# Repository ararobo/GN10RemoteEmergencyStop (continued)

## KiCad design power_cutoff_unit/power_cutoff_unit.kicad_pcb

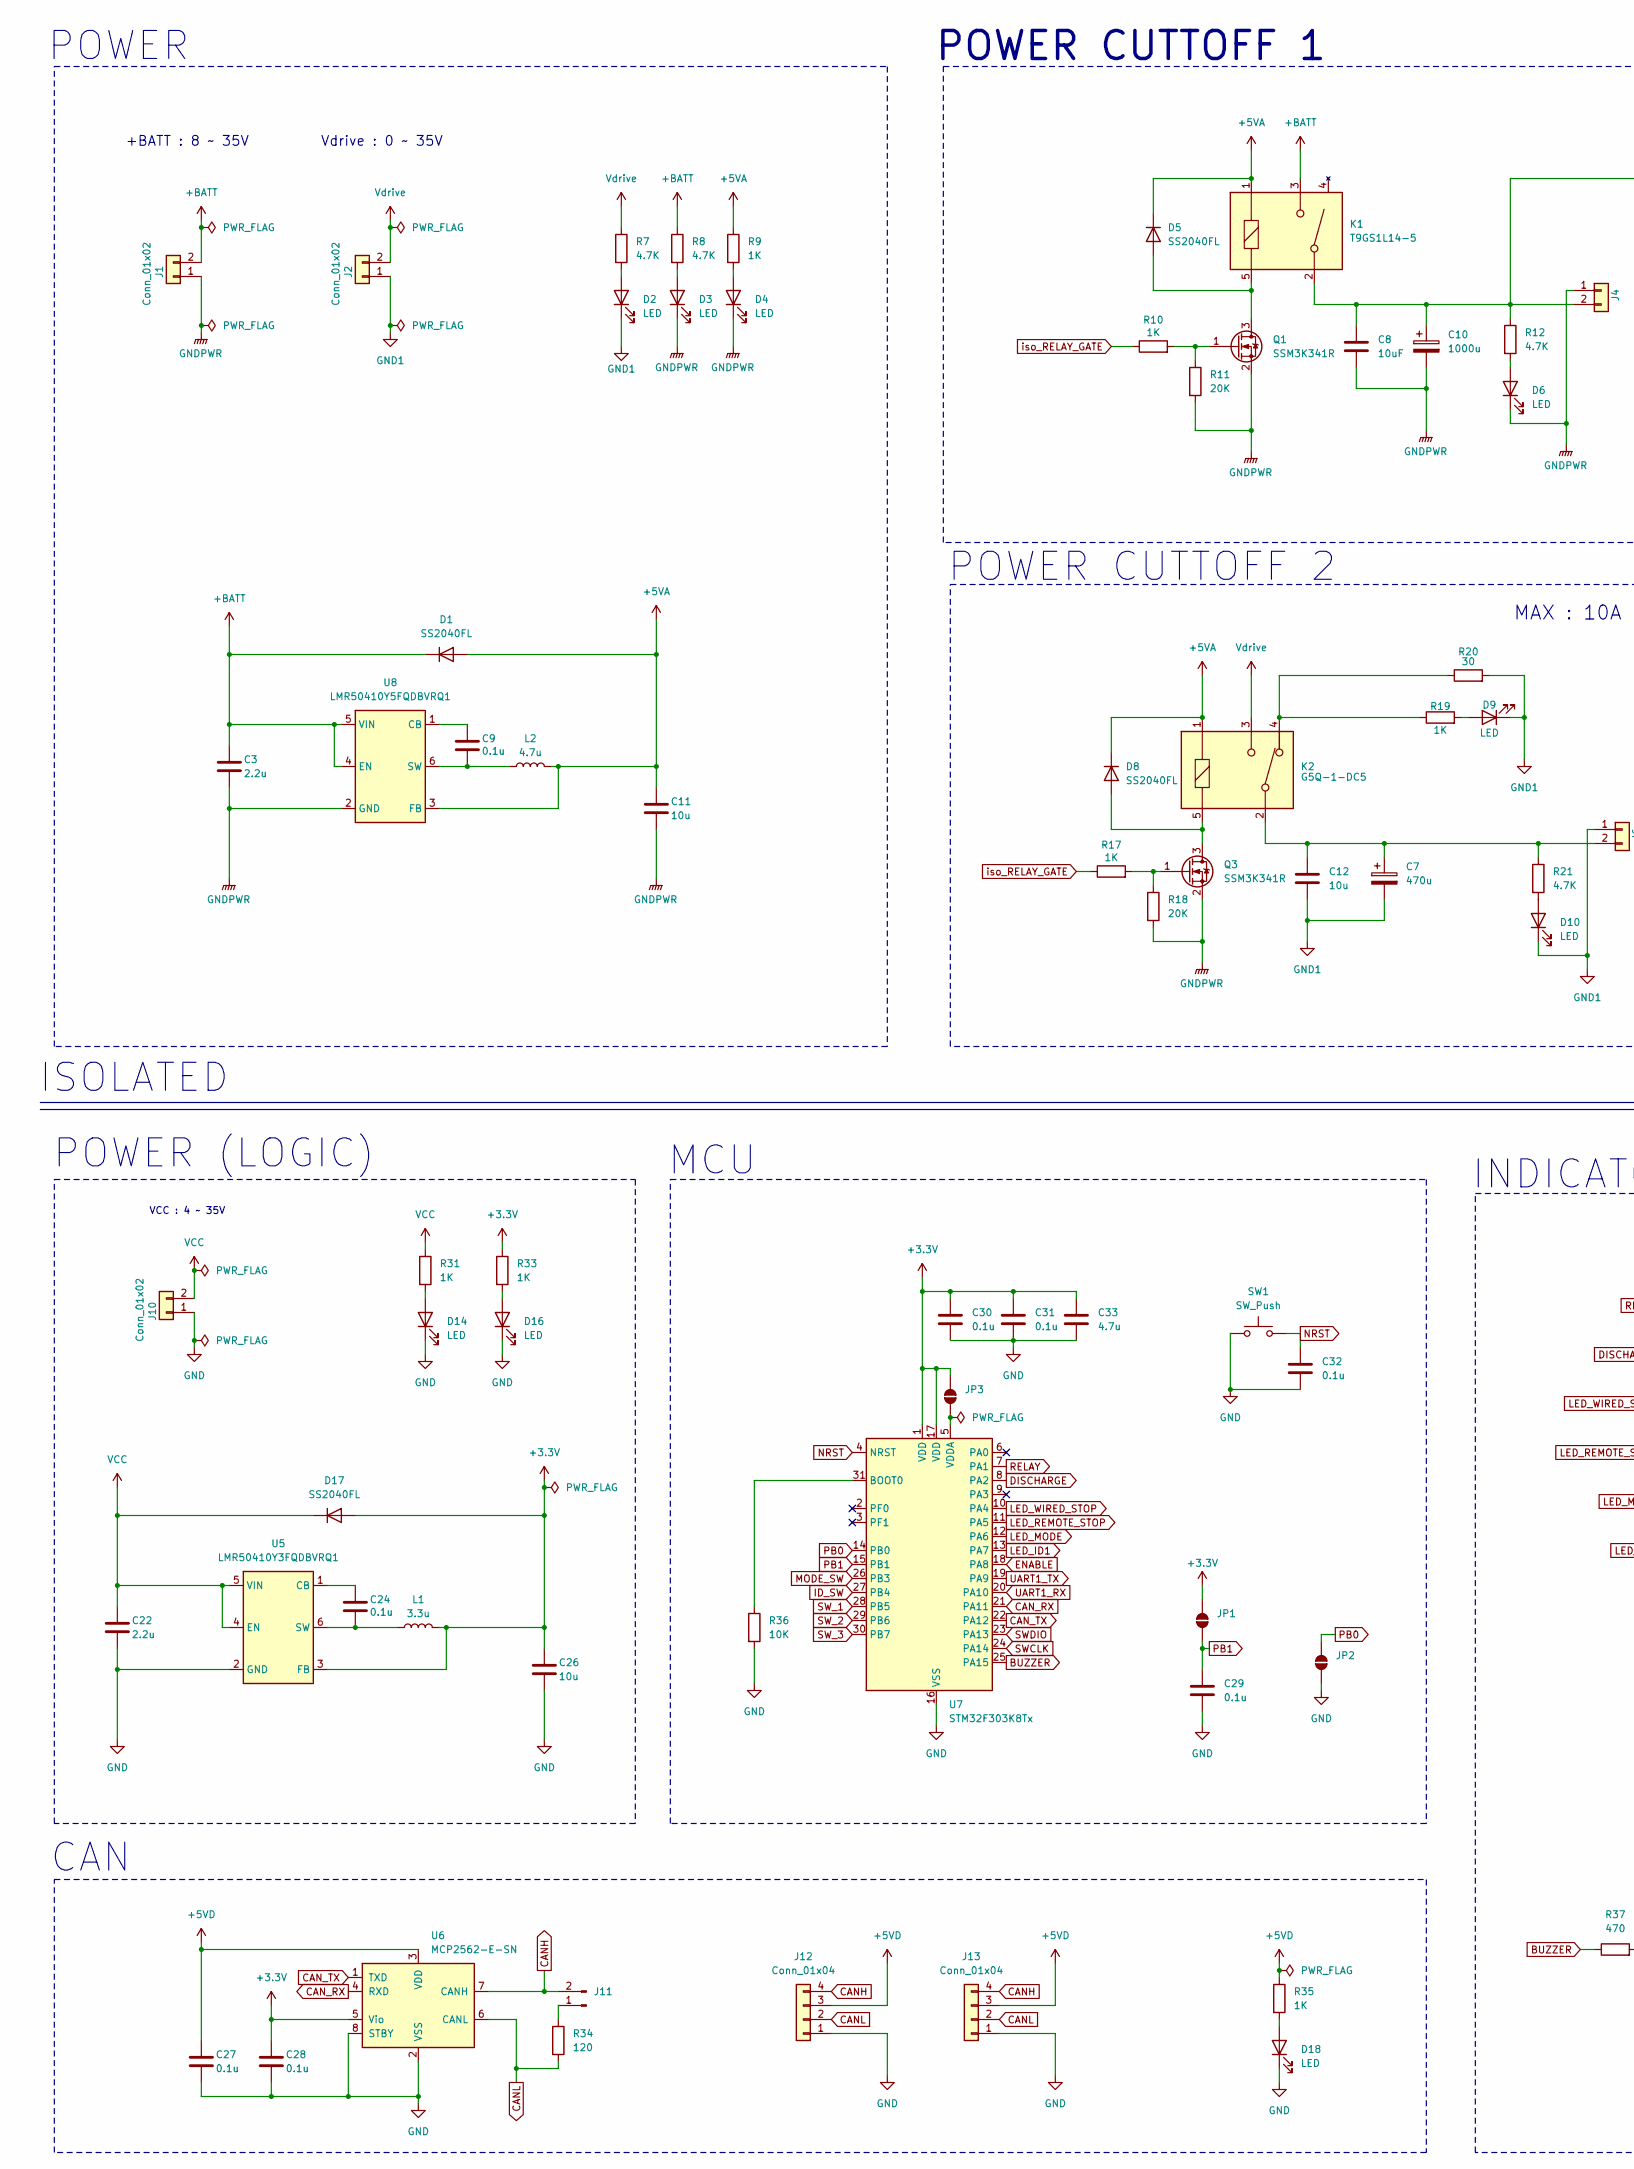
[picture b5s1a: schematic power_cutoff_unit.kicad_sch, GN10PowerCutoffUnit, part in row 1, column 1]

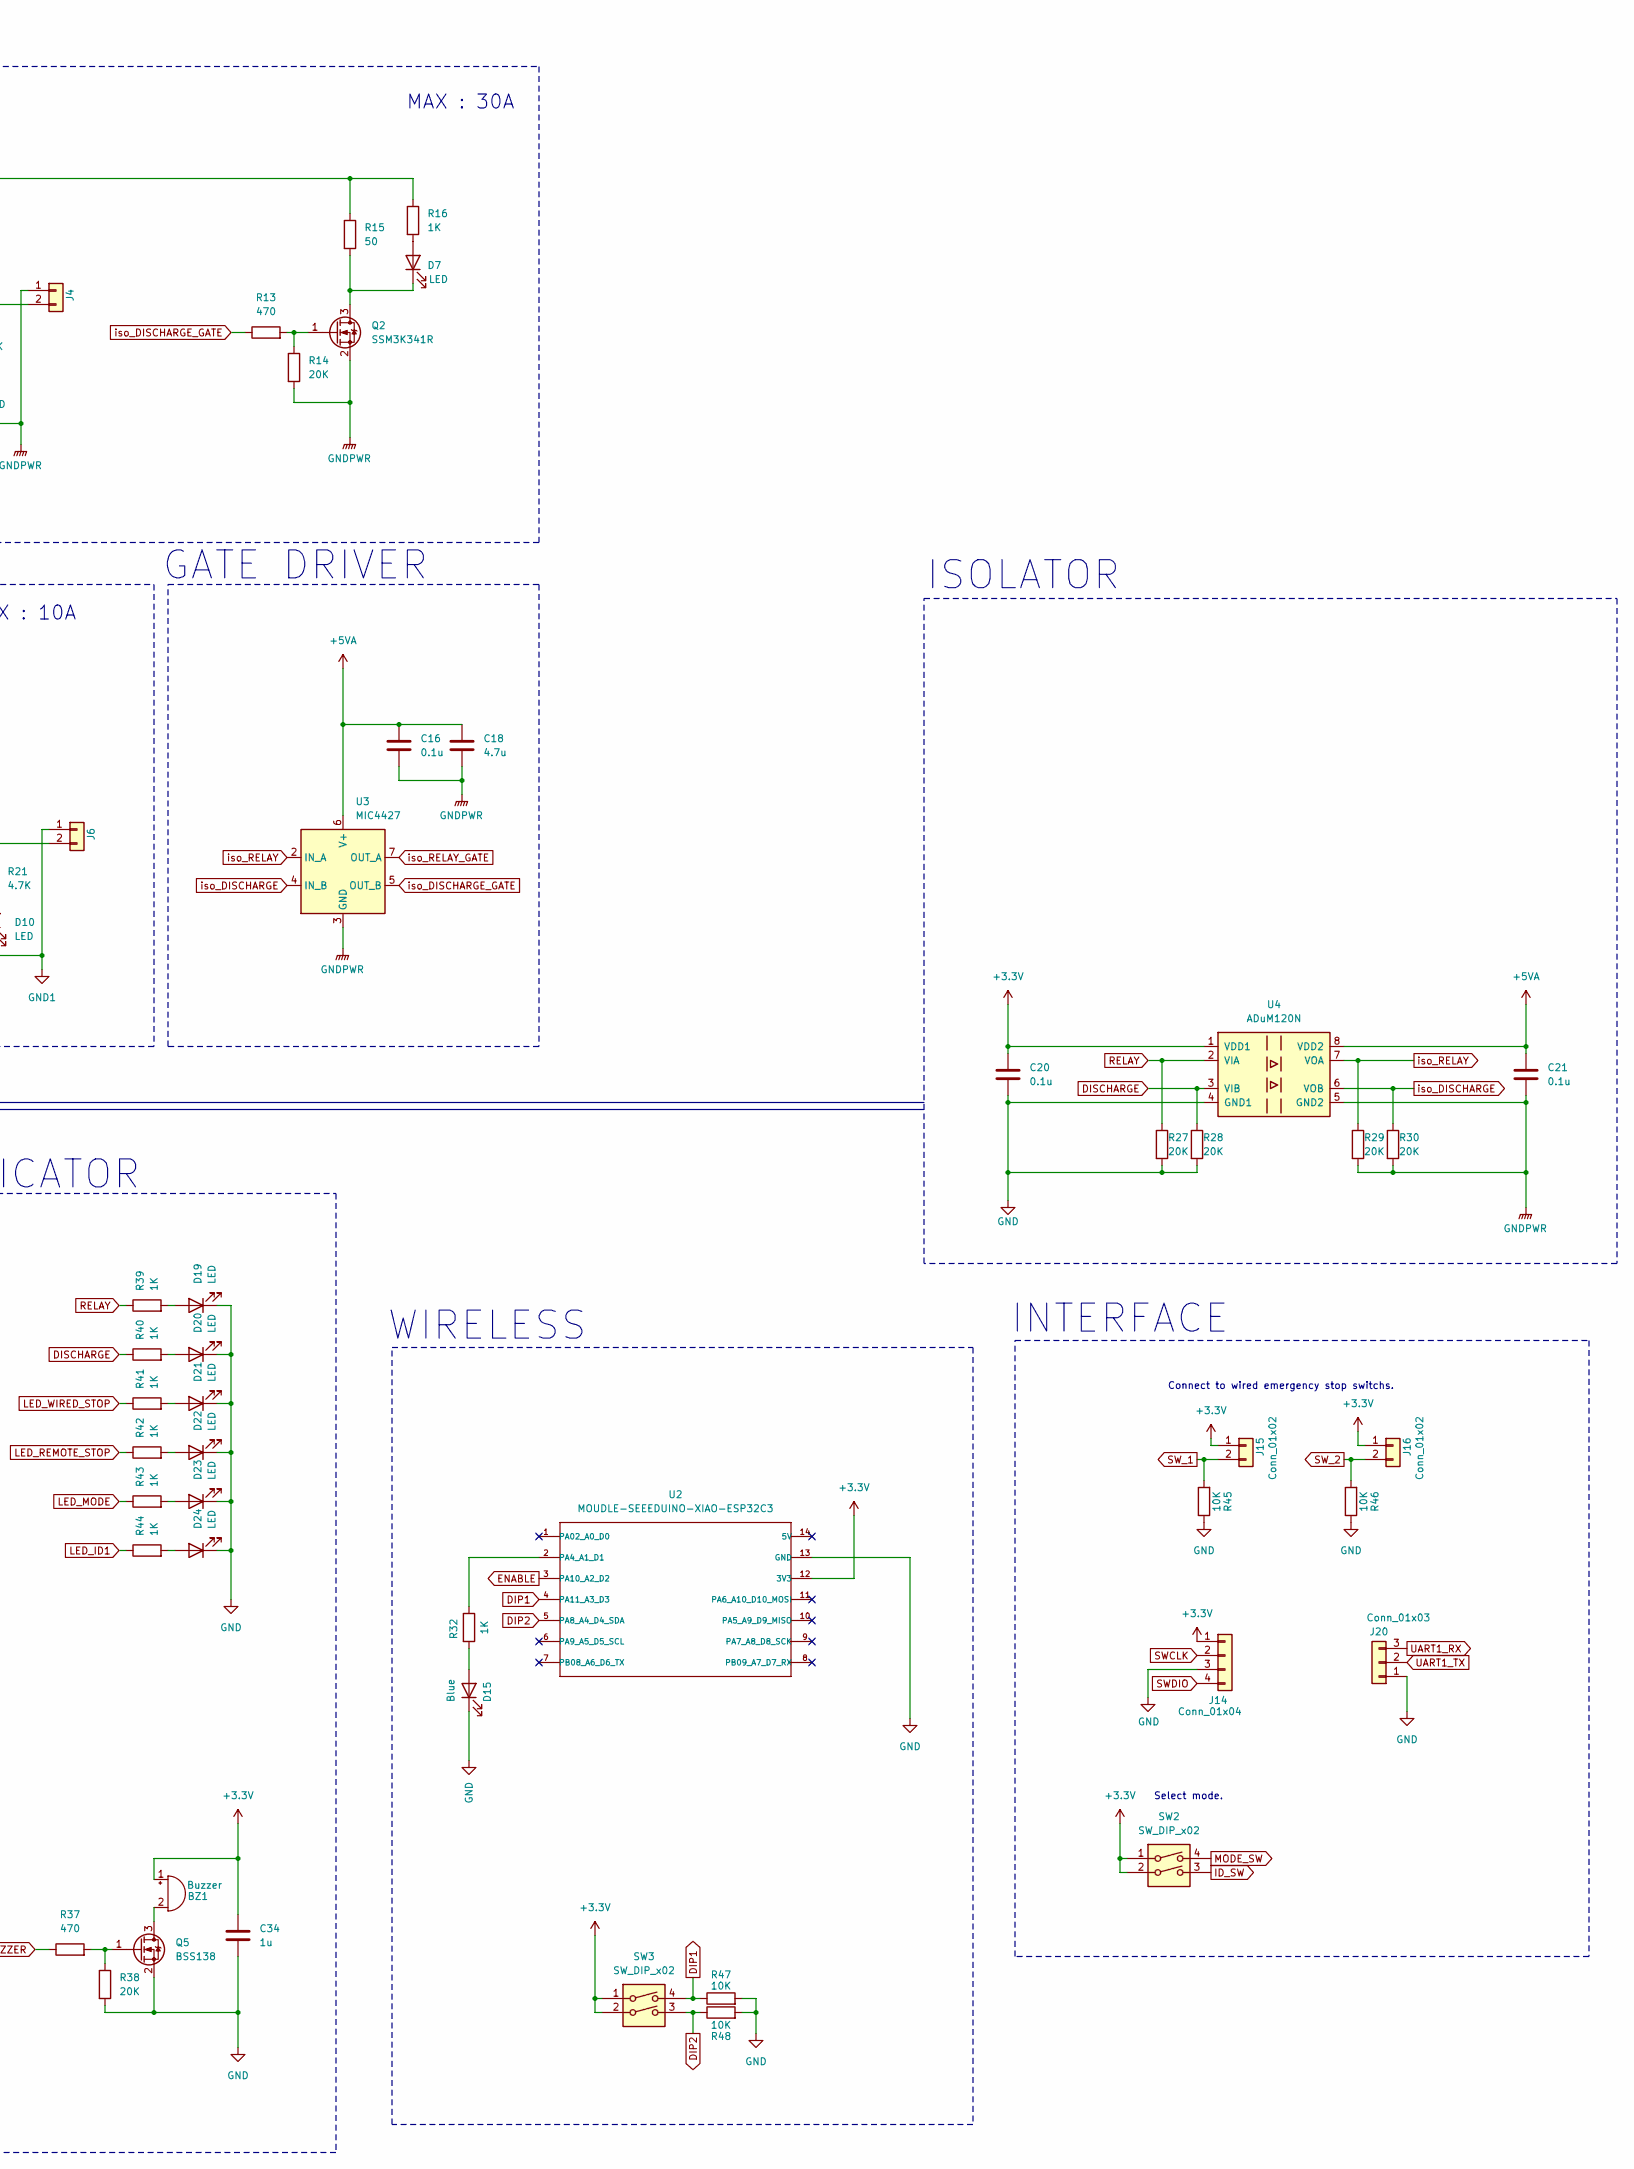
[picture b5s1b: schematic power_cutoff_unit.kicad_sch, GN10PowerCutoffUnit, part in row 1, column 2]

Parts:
BZ1: Buzzer; Buzzer_12x9.5RM7.6
C3, C22: 2.2u; C_0805_2012Metric
C7: 470u; CP_Radial_D12.5mm_P5.00mm
C8: 10uF; C_0805_2012Metric
C9, C16, C20, C21, C24, C27, C28, C29, C30, C31, C32: 0.1u; C_0402_1005Metric
C10: 1000u; CP_Radial_D16.0mm_P7.50mm
C11, C12, C26: 10u; C_0805_2012Metric
C18, C33: 4.7u; C_0603_1608Metric
C34: 1u; C_0402_1005Metric
D1, D5, D8, D17: SS2040FL; D_SOD-123F
D2, D3, D4, D6, D7, D9, D10, D14, D16, D18, D19, D20, D21, D22, D23, D24: LED; LED_0603_1608Metric
D15: Blue; LED_0603_1608Metric_Pad1.05x0.95mm_HandSolder
J1, J2: Conn_01x02; AMASS_XT60PW-M_1x02_P7.20mm_Horizontal
J4, J6: Conn_01x02; AMASS_XT60PW-F_1x02_P7.20mm_Horizontal
J10: Conn_01x02; AMASS_XT30U-M_1x02_P5.0mm_Vertical
J11: Conn_01x02_Pin; PinHeader_1x02_P2.54mm_Vertical
J12, J13: Conn_01x04; JST_XH_B4B-XH-A_1x04_P2.50mm_Vertical
J14: Conn_01x04; PinHeader_1x04_P2.54mm_Vertical
J15, J16: Conn_01x02; JST_XH_B2B-XH-A_1x02_P2.50mm_Vertical
J20: Conn_01x03; PinHeader_1x03_P2.54mm_Vertical
JP1, JP2, JP3: SolderJumper_2_Open; SolderJumper-2_P1.3mm_Open_RoundedPad1.0x1.5mm
K1: T9GS1L14-5; T9G
K2: G5Q-1-DC5; G5Q-1
L1: 3.3u; DEM2818C
L2: 4.7u; DEM2818C
Q1, Q2, Q3: SSM3K341R; SOT-23_Handsoldering
Q5: BSS138; SOT-23
R7, R8, R12, R21: 4.7K; R_0603_1608Metric
R9, R16, R19, R32: 1K; R_0402_1005Metric
R10, R17, R31, R33, R35, R39, R40, R41, R42, R43, R44: 1K; R_0603_1608Metric
R11, R14, R18, R27, R28, R29, R30, R38: 20K; R_0603_1608Metric
R13, R37: 470; R_0603_1608Metric
R15: 50; TO-263-2_TabPin1
R20: 30; TO-263-2_TabPin1
R34: 120; R_0603_1608Metric
R36, R45, R46, R47, R48: 10K; R_0603_1608Metric
SW1: SW_Push; SKRPABE010
SW2, SW3: SW_DIP_x02; SW_DIP_SPSTx02_Slide_Omron_A6H-2101_W6.15mm_P1.27mm
U2: MOUDLE-SEEEDUINO-XIAO-ESP32C3; MCU_Seeed_ESP32C3
U3: MIC4427; SOIC-8_3.9x4.9mm_P1.27mm
U4: ADuM120N; SOIC-8_3.9x4.9mm_P1.27mm
U5: LMR50410Y3FQDBVRQ1; SOT-23-6
U6: MCP2562-E-SN; SOIC-8_3.9x4.9mm_P1.27mm
U7: STM32F303K8Tx; LQFP-32_7x7mm_P0.8mm
U8: LMR50410Y5FQDBVRQ1; SOT-23-6

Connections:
+3.3V: BZ1.1 (+), C20.1, C26.1, C28.1, C30.1, C31.1, C33.1, C34.1, D17.2 (A), J14.1, J15.1, J16.1, JP1.2 (B), JP3.2 (B), L1.2, R33.1, SW2.1, SW2.2, SW3.1, SW3.2, U2.12 (3V3), U4.1 (VDD1), U5.3 (FB), U6.5 (Vio), U7.1 (VDD), U7.17 (VDD)
+5VA: C11.1, C16.1, C18.1, C21.1, D1.2 (A), D5.1 (K), D8.1 (K), K1.1, K2.1, L2.2, R9.1, U3.6 (V+), U4.8 (VDD2), U8.3 (FB)
+5VD: C27.1, J12.3, J13.3, R35.1, U6.3 (VDD)
+BATT: C3.1, D1.1 (K), J1.2, K1.3, R8.1, U8.4 (EN), U8.5 (VIN)
BUZZER: R37.1, U7.25 (PA15)
CANH: J11.2, J12.4, J13.4, U6.7 (CANH)
CANL: J12.2, J13.2, R34.2, U6.6 (CANL)
CAN_RX: U6.4 (RXD), U7.21 (PA11)
CAN_TX: U6.1 (TXD), U7.22 (PA12)
DIP1: R47.1, SW3.4, U2.4 (PA11_A3_D3)
DIP2: R48.1, SW3.3, U2.5 (PA8_A4_D4_SDA)
DISCHARGE: R28.1, R40.1, U4.3 (VIB), U7.8 (PA2)
ENABLE: U2.3 (PA10_A2_D2), U7.18 (PA8)
GND: C20.2, C22.2, C26.2, C27.2, C28.2, C29.2, C30.2, C31.2, C32.2, C33.2, C34.2, D14.1 (K), D15.1 (K), D16.1 (K), D18.1 (K), D19.1 (K), D20.1 (K), D21.1 (K), D22.1 (K), D23.1 (K), D24.1 (K), J10.1, J12.1, J13.1, J14.3, J20.1, JP2.1 (A), Q5.2 (S), R27.2, R28.2, R36.2, R38.2, R45.1, R46.1, R47.2, R48.2, SW1.1, U2.13 (GND), U4.4 (GND1), U5.2 (GND), U6.2 (VSS), U6.8 (STBY), U7.16 (VSS), U7.32 (VSS)
GND1: C7.2, C12.2, D2.1 (K), D9.1 (K), D10.1 (K), J2.1, J6.1, R20.2
GNDPWR: C3.2, C8.2, C10.2, C11.2, C16.2, C18.2, C21.2, D3.1 (K), D4.1 (K), D6.1 (K), J1.1, J4.1, Q1.2 (S), Q2.2 (S), Q3.2 (S), R11.2, R14.2, R18.2, R29.2, R30.2, U3.3 (GND), U4.5 (GND2), U8.2 (GND)
ID_SW: SW2.3, U7.27 (PB4)
LED_ID1: R44.1, U7.13 (PA7)
LED_MODE: R43.1, U7.12 (PA6)
LED_REMOTE_STOP: R42.1, U7.11 (PA5)
LED_WIRED_STOP: R41.1, U7.10 (PA4)
MODE_SW: SW2.4, U7.26 (PB3)
NRST: C32.1, SW1.2, U7.4 (NRST)
unnamed: BZ1.2 (-), Q5.3 (D)
unnamed: D2.2 (A), R7.2
unnamed: D3.2 (A), R8.2
unnamed: D4.2 (A), R9.2
unnamed: D5.2 (A), K1.5, Q1.3 (D)
unnamed: D6.2 (A), R12.2
unnamed: D7.2 (A), R16.2
unnamed: D7.1 (K), Q2.3 (D), R15.2
unnamed: D8.2 (A), K2.5, Q3.3 (D)
unnamed: D9.2 (A), R19.2
unnamed: D10.2 (A), R21.2
unnamed: D14.2 (A), R31.2
unnamed: D15.2 (A), R32.2
unnamed: D16.2 (A), R33.2
unnamed: D18.2 (A), R35.2
unnamed: D19.2 (A), R39.2
unnamed: D20.2 (A), R40.2
unnamed: D21.2 (A), R41.2
unnamed: D22.2 (A), R42.2
unnamed: D23.2 (A), R43.2
unnamed: D24.2 (A), R44.2
unnamed: C8.1, C10.1, J4.2, K1.2, R12.1, R15.1, R16.1
unnamed: C7.1, C12.1, J6.2, K2.2, R21.1
unnamed: J11.1, R34.1
unnamed: JP3.1 (A), U7.5 (VDDA)
unnamed: K2.4, R19.1, R20.1
unnamed: Q1.1 (G), R10.2, R11.1
unnamed: Q2.1 (G), R13.2, R14.1
unnamed: Q3.1 (G), R17.2, R18.1
unnamed: Q5.1 (G), R37.2, R38.1
unnamed: R32.1, U2.2 (PA4_A1_D1)
unnamed: C24.1, U5.1 (CB)
unnamed: C24.2, L1.1, U5.6 (SW)
unnamed: R36.1, U7.31 (BOOT0)
unnamed: C9.1, U8.1 (CB)
unnamed: C9.2, L2.1, U8.6 (SW)
PB0: JP2.2 (B), U7.14 (PB0)
PB1: C29.1, JP1.1 (A), U7.15 (PB1)
RELAY: R27.1, R39.1, U4.2 (VIA), U7.7 (PA1)
SWCLK: J14.2, U7.24 (PA14)
SWDIO: J14.4, U7.23 (PA13)
SW_1: J15.2, R45.2, U7.28 (PB5)
SW_2: J16.2, R46.2, U7.29 (PB6)
SW_3: U7.30 (PB7)
UART1_RX: J20.3, U7.20 (PA10)
UART1_TX: J20.2, U7.19 (PA9)
VCC: C22.1, D17.1 (K), J10.2, R31.1, U5.4 (EN), U5.5 (VIN)
Vdrive: J2.2, K2.3, R7.1
iso_DISCHARGE: R30.1, U3.4 (IN_B), U4.6 (VOB)
iso_DISCHARGE_GATE: R13.1, U3.5 (OUT_B)
iso_RELAY: R29.1, U3.2 (IN_A), U4.7 (VOA)
iso_RELAY_GATE: R10.1, R17.1, U3.7 (OUT_A)

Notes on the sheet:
ISOLATED
INDICATOR
POWER CUTTOFF 1
WIRELESS
POWER
MCU
POWER CUTTOFF 2
INTERFACE
VCC : 4 ~ 35V
+BATT : 8 ~ 35V
Connect to wired emergency stop switchs.
POWER (LOGIC)
CAN
ISOLATOR
Vdrive : 0 ~ 35V
GATE DRIVER
MAX : 10A
MAX : 30A
Select mode.

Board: 2 copper layers, 113 parts (21 on the bottom side), 74 nets, no tracks yet.

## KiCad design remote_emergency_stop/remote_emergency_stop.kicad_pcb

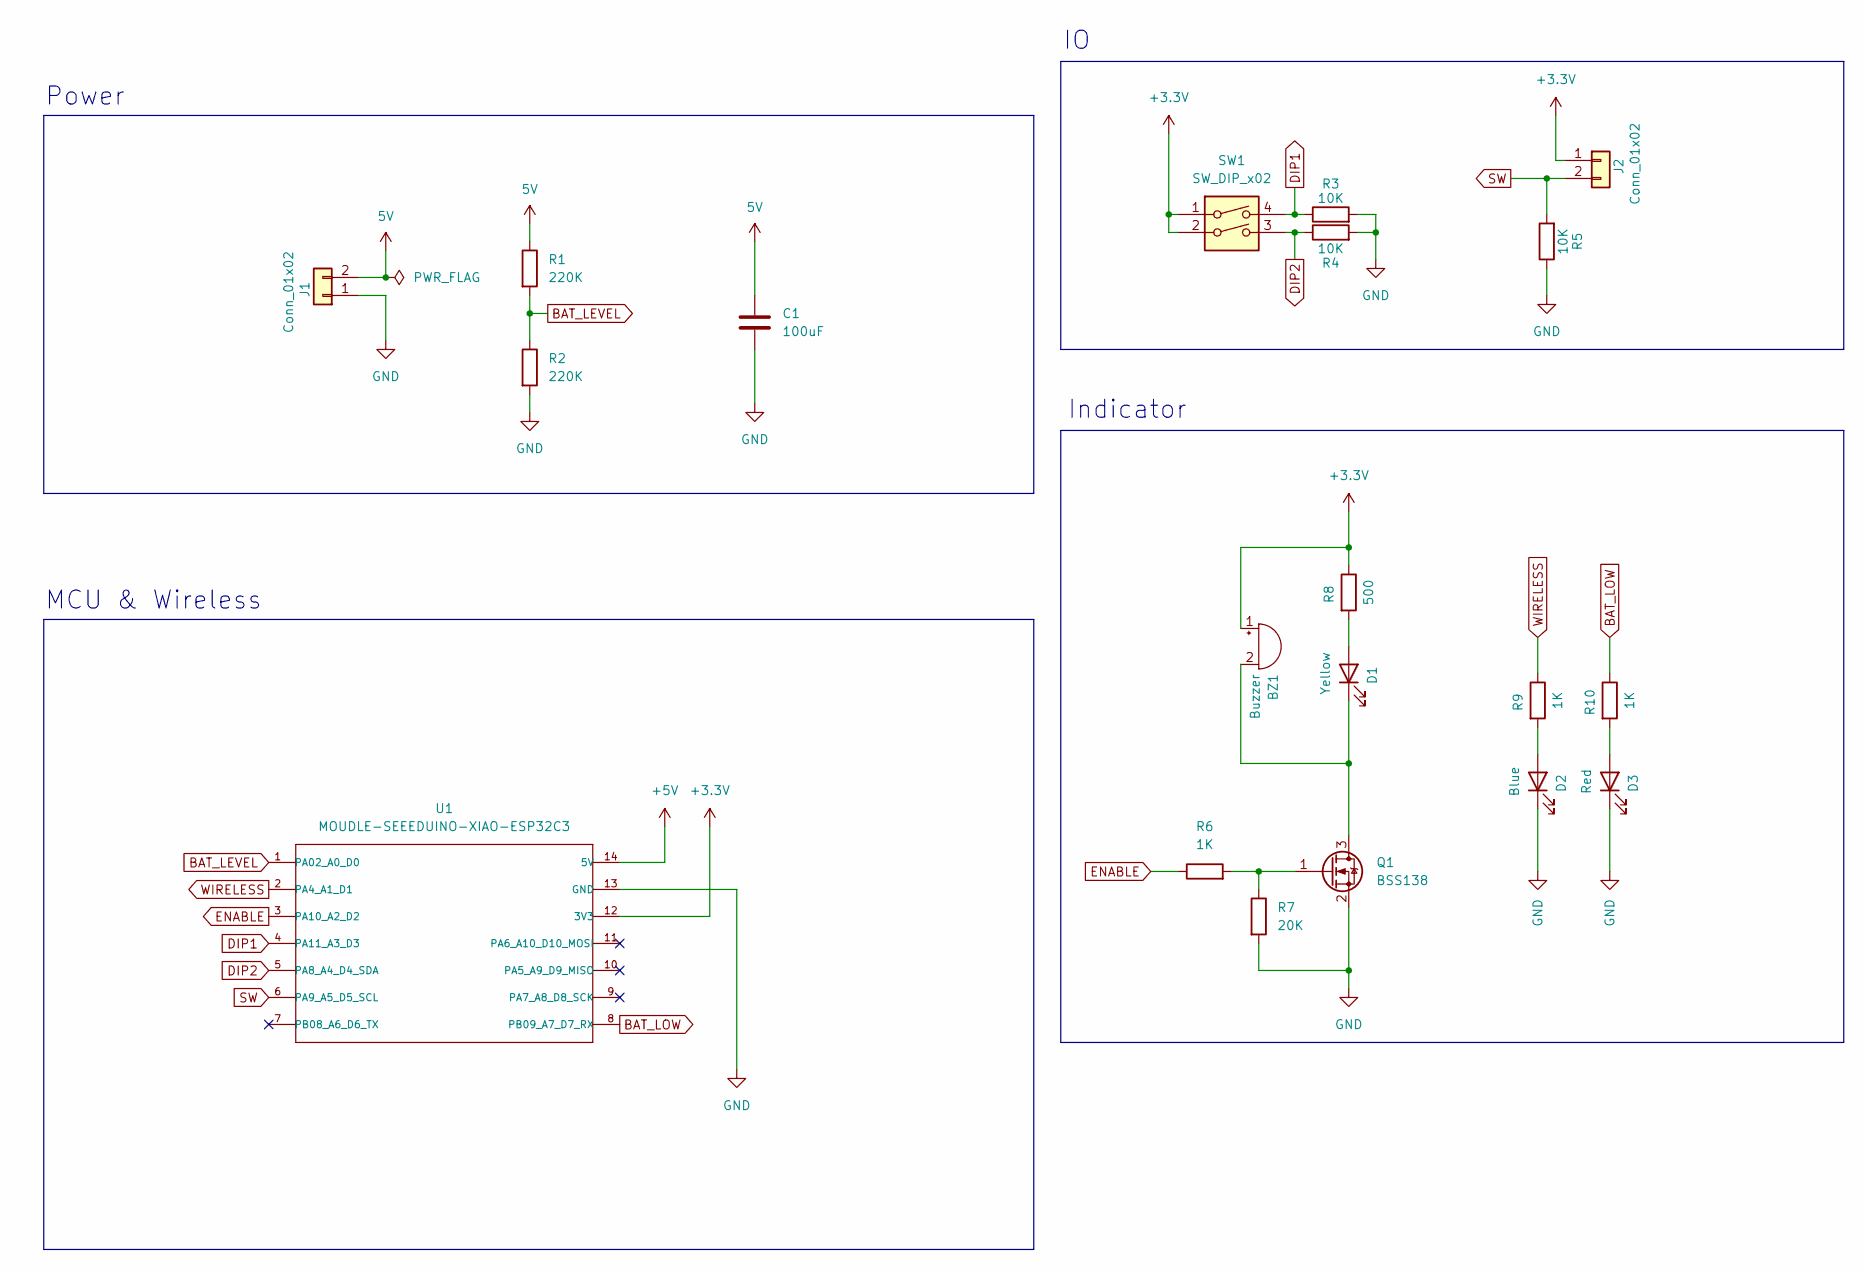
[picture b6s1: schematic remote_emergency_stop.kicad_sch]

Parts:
BZ1: Buzzer; Buzzer_12x9.5RM7.6
C1: 100uF; CP_Radial_D5.0mm_P2.00mm
D1: Yellow; LED_0603_1608Metric_Pad1.05x0.95mm_HandSolder
D2: Blue; LED_0603_1608Metric_Pad1.05x0.95mm_HandSolder
D3: Red; LED_0603_1608Metric_Pad1.05x0.95mm_HandSolder
J1: Conn_01x02; AMASS_XT30PW-M_1x02_P2.50mm_Horizontal
J2: Conn_01x02; JST_XH_S2B-XH-A_1x02_P2.50mm_Horizontal
Q1: BSS138; SOT-23
R1, R2: 220K; R_0603_1608Metric
R3, R4, R5: 10K; R_0603_1608Metric
R6, R9, R10: 1K; R_0603_1608Metric
R7: 20K; R_0603_1608Metric
R8: 500; R_0603_1608Metric
SW1: SW_DIP_x02; SW_DIP_SPSTx02_Slide_Omron_A6H-2101_W6.15mm_P1.27mm
U1: MOUDLE-SEEEDUINO-XIAO-ESP32C3; MCU_Seeed_ESP32C3

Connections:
5V: C1.1, J1.2, R1.1
+3.3V: BZ1.1 (+), J2.1, R8.1, SW1.1, SW1.2, U1.12 (3V3)
+5V: U1.14 (5V)
BAT_LEVEL: R1.2, R2.1, U1.1 (PA02_A0_D0)
BAT_LOW: R10.1, U1.8 (PB09_A7_D7_RX)
DIP1: R3.1, SW1.4, U1.4 (PA11_A3_D3)
DIP2: R4.1, SW1.3, U1.5 (PA8_A4_D4_SDA)
ENABLE: R6.1, U1.3 (PA10_A2_D2)
GND: C1.2, D2.1 (K), D3.1 (K), J1.1, Q1.2 (S), R2.2, R3.2, R4.2, R5.1, R7.2, U1.13 (GND)
unnamed: BZ1.2 (-), D1.1 (K), Q1.3 (D)
unnamed: D1.2 (A), R8.2
unnamed: D2.2 (A), R9.2
unnamed: D3.2 (A), R10.2
unnamed: Q1.1 (G), R6.2, R7.1
SW: J2.2, R5.2, U1.6 (PA9_A5_D5_SCL)
WIRELESS: R9.1, U1.2 (PA4_A1_D1)

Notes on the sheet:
MCU & Wireless
Indicator
Power

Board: 2 copper layers, 20 parts (0 on the bottom side), 15 nets, no tracks yet.

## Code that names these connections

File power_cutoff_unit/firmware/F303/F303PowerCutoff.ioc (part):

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Mcu.Name=STM32F303K(6-8)Tx
Mcu.Package=LQFP32
Mcu.UserName=STM32F303K8Tx
PA1.GPIOParameters=GPIO_Label
PA1.GPIO_Label=DISCHARGE
PA1.Signal=GPIO_Output
PA10.Mode=Asynchronous
PA10.Signal=USART1_RX
PA11.Mode=CAN_Activate
PA11.Signal=CAN_RX
PA12.Mode=CAN_Activate
PA12.Signal=CAN_TX
PA13.Mode=Serial_Wire
PA13.Signal=SYS_JTMS-SWDIO
PA14.Mode=Serial_Wire
PA14.Signal=SYS_JTCK-SWCLK
PA15.GPIOParameters=GPIO_Label
PA15.GPIO_Label=BUZZER
PA15.Signal=GPIO_Output
PA2.GPIOParameters=GPIO_Label
PA2.GPIO_Label=RELAY_EN
PA2.Signal=GPIO_Output
PA4.GPIOParameters=GPIO_Label
PA4.GPIO_Label=LED_WIRED_STOP
PA4.Signal=GPIO_Output
PA5.GPIOParameters=GPIO_Label
PA5.GPIO_Label=LED_REMOTE_STOP
PA5.Signal=GPIO_Output
PA6.GPIOParameters=GPIO_Label
PA6.GPIO_Label=LED_MODE
PA6.Signal=GPIO_Output
PA7.GPIOParameters=GPIO_Label
PA7.GPIO_Label=LED_ID1
PA7.Signal=GPIO_Output
PA8.GPIOParameters=GPIO_Label
PA8.GPIO_Label=ENABLE
PA8.Signal=GPIO_Input
PA9.Mode=Asynchronous
PA9.Signal=USART1_TX
PB3.GPIOParameters=GPIO_Label
PB3.GPIO_Label=DIP_1
PB3.Signal=GPIO_Input
PB4.GPIOParameters=GPIO_Label
PB4.GPIO_Label=DIP_2
PB4.Signal=GPIO_Input
PB5.GPIOParameters=GPIO_Label
PB5.GPIO_Label=SW_1
PB5.Signal=GPIO_Input
PB6.GPIOParameters=GPIO_Label
PB6.GPIO_Label=SW_2
PB6.Signal=GPIO_Input
PB7.GPIOParameters=GPIO_Label
PB7.GPIO_Label=SW_3
PB7.Signal=GPIO_Input
RCC.HSEPLLFreq_Value=8000000
RCC.HSE_VALUE=8000000
RCC.SYSCLKFreq_VALUE=64000000
RCC.SYSCLKSourceVirtual=RCC_SYSCLKSOURCE_PLLCLK
board=custom

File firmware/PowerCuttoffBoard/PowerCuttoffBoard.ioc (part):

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Mcu.Name=STM32F303K(6-8)Tx
Mcu.Package=LQFP32
Mcu.UserName=STM32F303K8Tx
PA10.Mode=Asynchronous
PA10.Signal=USART1_RX
PA11.Mode=CAN_Activate
PA11.Signal=CAN_RX
PA12.Mode=CAN_Activate
PA12.Signal=CAN_TX
PA13.Mode=Serial_Wire
PA13.Signal=SYS_JTMS-SWDIO
PA14.Mode=Serial_Wire
PA14.Signal=SYS_JTCK-SWCLK
PA15.GPIOParameters=GPIO_PuPd,GPIO_Label
PA15.GPIO_Label=DIP4
PA15.GPIO_PuPd=GPIO_PULLDOWN
PA15.Signal=GPIO_Input
PA2.Mode=Asynchronous
PA2.Signal=USART2_TX
PA3.Mode=Asynchronous
PA3.Signal=USART2_RX
PA5.GPIOParameters=GPIO_Label
PA5.GPIO_Label=LED2
PA5.Signal=GPIO_Output
PA6.GPIOParameters=GPIO_Label
PA6.GPIO_Label=LED1
PA6.Signal=GPIO_Output
PA7.GPIOParameters=GPIO_Label
PA7.GPIO_Label=LED_CONNECTION
PA7.Signal=GPIO_Output
PA9.Mode=Asynchronous
PA9.Signal=USART1_TX
PB0.GPIOParameters=GPIO_Label
PB0.GPIO_Label=LED_DEBUG
PB0.Signal=GPIO_Output
PB1.GPIOParameters=GPIO_Label
PB1.GPIO_Label=LED_ERROR
PB1.Signal=GPIO_Output
PB3.GPIOParameters=GPIO_PuPd,GPIO_Label
PB3.GPIO_Label=DIP3
PB3.GPIO_PuPd=GPIO_PULLDOWN
PB3.Signal=GPIO_Input
PB4.GPIOParameters=GPIO_PuPd,GPIO_Label
PB4.GPIO_Label=DIP2
PB4.GPIO_PuPd=GPIO_PULLDOWN
PB4.Signal=GPIO_Input
PB5.GPIOParameters=GPIO_PuPd,GPIO_Label
PB5.GPIO_Label=DIP1
PB5.GPIO_PuPd=GPIO_PULLDOWN
PB5.Signal=GPIO_Input
PB6.GPIOParameters=GPIO_Label
PB6.GPIO_Label=RELAY_A
PB6.Signal=GPIO_Output
PB7.GPIOParameters=GPIO_Label
PB7.GPIO_Label=RELAY_B
PB7.Signal=GPIO_Output
RCC.HSEPLLFreq_Value=16000000
RCC.HSE_VALUE=16000000
RCC.SYSCLKFreq_VALUE=64000000
RCC.SYSCLKSourceVirtual=RCC_SYSCLKSOURCE_PLLCLK
board=custom

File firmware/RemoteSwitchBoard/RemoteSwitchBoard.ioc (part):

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Mcu.Name=STM32F303K(6-8)Tx
Mcu.Package=LQFP32
Mcu.UserName=STM32F303K8Tx
PA0.GPIOParameters=GPIO_Label
PA0.GPIO_Label=Buzzer
PA0.Signal=GPIO_Output
PA1.GPIOParameters=GPIO_PuPd,GPIO_Label
PA1.GPIO_Label=emstop
PA1.GPIO_PuPd=GPIO_PULLDOWN
PA1.Signal=GPIO_Input
PA10.Mode=Asynchronous
PA10.Signal=USART1_RX
PA11.GPIOParameters=GPIO_Label
PA11.GPIO_Label=LED_5
PA11.Signal=GPIO_Output
PA12.GPIOParameters=GPIO_Label
PA12.GPIO_Label=LED_6
PA12.Signal=GPIO_Output
PA13.Signal=SYS_JTMS-SWDIO
PA14.Signal=SYS_JTCK-SWCLK
PA15.GPIOParameters=GPIO_PuPd,GPIO_Label
PA15.GPIO_Label=DIP_4
PA15.GPIO_PuPd=GPIO_PULLDOWN
PA15.Signal=GPIO_Input
PA2.Mode=Asynchronous
PA2.Signal=USART2_TX
PA3.Mode=Asynchronous
PA3.Signal=USART2_RX
PA4.GPIOParameters=GPIO_Label
PA4.GPIO_Label=LED_3
PA4.Signal=GPIO_Output
PA6.GPIOParameters=GPIO_Label
PA6.GPIO_Label=LED_1
PA6.Signal=GPIO_Output
PA8.GPIOParameters=GPIO_Label
PA8.GPIO_Label=LED_4
PA8.Signal=GPIO_Output
PA9.Mode=Asynchronous
PA9.Signal=USART1_TX
PB3.GPIOParameters=GPIO_PuPd,GPIO_Label
PB3.GPIO_Label=DIP_3
PB3.GPIO_PuPd=GPIO_PULLDOWN
PB3.Signal=GPIO_Input
PB4.GPIOParameters=GPIO_PuPd,GPIO_Label
PB4.GPIO_Label=DIP_2
PB4.GPIO_PuPd=GPIO_PULLDOWN
PB4.Signal=GPIO_Input
PB5.GPIOParameters=GPIO_PuPd,GPIO_Label
PB5.GPIO_Label=DIP_1
PB5.GPIO_PuPd=GPIO_PULLDOWN
PB5.Signal=GPIO_Input
PB6.GPIOParameters=GPIO_Label
PB6.GPIO_Label=bustop
PB6.Signal=GPIO_Input
PB7.GPIOParameters=GPIO_Label
PB7.GPIO_Label=LED_emstop
PB7.Signal=GPIO_Output
RCC.HSEPLLFreq_Value=8000000
RCC.HSE_VALUE=8000000
RCC.SYSCLKFreq_VALUE=64000000
RCC.SYSCLKSourceVirtual=RCC_SYSCLKSOURCE_PLLCLK
board=custom

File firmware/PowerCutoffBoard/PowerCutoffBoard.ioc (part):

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Mcu.Name=STM32G431C(6-8-B)Ux
Mcu.Package=UFQFPN48
Mcu.UserName=STM32G431CBUx
PA10.Mode=Asynchronous
PA10.Signal=USART1_RX
PA11.Mode=FDCAN_Activate
PA11.Signal=FDCAN1_RX
PA12.Mode=FDCAN_Activate
PA12.Signal=FDCAN1_TX
PA13.Mode=Serial_Wire
PA13.Signal=SYS_JTMS-SWDIO
PA14.Mode=Serial_Wire
PA14.Signal=SYS_JTCK-SWCLK
PA2.Signal=GPIO_Output
PA3.Signal=GPIO_Output
PA4.Signal=GPIO_Output
PA5.Signal=GPIO_Output
PA6.Signal=GPIO_Output
PA7.Signal=GPIO_Output
PA9.Mode=Asynchronous
PA9.Signal=USART1_TX
PB0.Signal=GPIO_Output
PB12.Signal=GPIO_Output
PB13.Signal=GPIO_Output
PB14.Signal=GPIO_Output
PB15.Signal=GPIO_Output
PB4.GPIOParameters=GPIO_Label
PB4.GPIO_Label=LED_Connection
PB4.Signal=GPIO_Output
PB5.GPIOParameters=GPIO_Label
PB5.GPIO_Label=LED_Debug
PB5.Signal=GPIO_Output
PB6.GPIOParameters=GPIO_Label
PB6.GPIO_Label=LED_Error
PB6.Signal=GPIO_Output
PC10.Mode=Asynchronous
PC10.Signal=USART3_TX
PC11.Mode=Asynchronous
PC11.Signal=USART3_RX
PC4.Signal=GPIO_Output
PC6.Signal=GPIO_Output
PF0-OSC_IN.Mode=HSE-External-Oscillator
PF0-OSC_IN.Signal=RCC_OSC_IN
PF1-OSC_OUT.Mode=HSE-External-Oscillator
PF1-OSC_OUT.Signal=RCC_OSC_OUT
RCC.HSE_VALUE=24000000
RCC.SYSCLKFreq_VALUE=96000000
RCC.SYSCLKSource=RCC_SYSCLKSOURCE_PLLCLK
board=custom

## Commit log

2024-09-25 プロジェクト作成
2024-10-01 通信モジュール決定
2024-10-03 こりゃだめだ、ユーザーインタフェイスが整ってない。
2024-10-03 遠隔非常停止は回路だけ完成した気がする
2024-10-03 ESP32とIOをすこしまとめた
2024-10-05 遠隔非常停止のフットプリント決定した。回路にコンデンサ追加
2024-10-05 駆動系電源社団モジュールの回路設計開始。リレーのシンボル作成。STM32も選定。
2024-10-07 駆動系側の電圧変換ICを追加した
2024-10-09 難しくてわかんないッピ
2024-10-14 細かい部品追加した。
2024-10-14 5Vを選択的にした
2024-10-14 CubeMXでプロジェクト作成
2024-10-14 MOSFET修正とCの値入れた。
2024-10-19 STM32のピン配置とインジケーターを追加
2024-10-19 ピン名等見直し
2024-10-19 add:PDF
2024-10-19 パスコン追加、電源追加(修正)
2024-10-19 3.3Vをスイッチングレギュレータにして、5Vの電源生成を消した。
2024-10-19 リレー増築中
2024-10-20 リレー3個にしてゲートドライバも追加
2024-10-20 DLC通るようにした
2024-10-20 日付変更
2024-10-20 配置考え直す。
2024-10-21 何したか覚えてないけど。
2024-10-22 電圧書いた。配置きれいにした。
2024-10-22 PCBに入ったけどコンデンサの放電用抵抗を小さくしたい。
2024-10-24 配置考え始めた
2024-10-28 PCBの配置考え中
2024-10-28 大電流部品の主な配置を考えた。
2024-10-29 重要な制御系部品の配置を少し考えた。
2024-11-01 高額だし、大きいので5Vラインのスイッチングレギュレーターを変更。
2024-11-03 現時点を記録
2024-11-03 電源遮断ユニット：ファームをiocだけにして、kicadのプロジェクトを新規作成。
2024-11-04 仕様部品を記載しREADMEを更新
2024-11-04 部品表更新
2024-11-07 集積回路だけ追加
2024-11-07 必要そうなシンボルとフットプリント追加
2024-11-10 自動生成されるバックアップ用のzipを消去。
2024-11-19 電源回りの回路をいい加減に作った。
2024-11-20 仕様書追記。リレーの追加。
2024-11-20 gitignoreのパスがバックスラッシュになっていたので修正
2024-11-21 リレーの回路を組み立てた。
2024-12-17 update: Indicator
2024-12-17 Good bye ESP32 !!!!!!!
2024-12-19 add: RNBD451
2024-12-20 RNBD451のFPを作ってる。
2024-12-22 RNBD451のフットプリント完成。
2024-12-29 少しだけ配線した。
2025-02-04 update: README
2025-02-04 add: Wio-5E
2025-02-16 revised: all
2025-02-18 update: PowerCutoffBoard's schematic.
2025-02-19 add: parts list. update: schematic.
2025-03-29 delete
2025-04-02 generate: gaber PowerCutoffBoard2
2025-05-02 PCB:Temporarily correct placement of parts
2025-05-03 update:PCB updated
2025-05-25 fix:schematic
2025-05-25 style
2025-08-07 Wired PowerCutoffBoard1
2025-08-09 RemoteSwitchBoard sch
2025-08-13 update:PowerCutoffBoard1
2025-08-30 update:配置の変更,配線の改善
2025-09-01 update:取捨選択とノイズ対策
2025-09-01 add:gaber
2025-09-12 add:generate code
2025-09-12 update:makefile
2025-09-12 remove:build
2025-09-12 add:gitignore, write.sh
2025-09-15 add:relay pin
2025-09-29 update:gpio
2025-10-06 update:start state
